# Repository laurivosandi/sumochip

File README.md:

# SumoCHIP

SumoCHIP is an extremely low-budget robotics platform based on CHIP single-board
computer. SumoCHIP is designed for teaching soldering, electronics, programming
and networking.

## Documentation

Bill of materials, instructions for building the robot and setting up the software are available [here](doc/index.md).
Translations are very much welcome.
See below how you can contribute!

## Demo

This is how the robot looks like once assembled:

Here's a video of two sumorobots battling in the sumo ring:

## Kits

Being completely open hardware you can order the components and assemble the
robot yourself with the prices stated in the [bill of materials](doc/bom.md) page,
expect to spend around 30 USD per robot.
Robotics Club of Estonian IT College provides kits within EU which saves
you the hassle of purchasing invidual components online.

| Description                                                    | Price                         |
|----------------------------------------------------------------|-------------------------------|
| SumoCHIP PCB and solderable components only                    | 20 EUR + recommended donation |
| Everything except [C.H.I.P.](http://getchip.com/products/chip) | 40 EUR + recommended donation |
| All in one batteries included kit                              | 50 EUR + recommended donation |

When ordering please specify whether you want PCB to be soldered or not,
soldered board adds extra 10 EUR to the price. We can also ship custom
configurations of components.
Donations are used to renew the equipment of robotics club so we could continue doing cool stuff!

To order send us e-mail and we'll reply with an invoice PDF.
Within EU standard [SEPA](https://en.wikipedia.org/wiki/Single_Euro_Payments_Area)
payments are expected. Once payment is received the kits will be shipped with
standard mail services once a week.

## Software

The current implementation is based on Python and Flask.
In future we might add
[kernel module for generating fine grained PWM signals](https://github.com/tanzilli/soft_pwm)
to achieve better timing granularity for servo motors.

## Contributing

Improvements and translations are very much welcome.
The contents of this Git repository are published under very liberal [MIT license](LICENSE).
Just register an account here at GitHub and hit the Fork button in the top right corner,
this shall make a copy of the source code repository under your GitHub account.
Make the necessary modifications in your repository and once ready
make a [pull request](https://help.github.com/articles/about-pull-requests/)
to get your changes merged. All contributors shall be mentioned in [the contributors list](CONTRIBUTORS.md).
We don't expect you to sign a contributor license agreement,
but you should not forget that as this project is distributed under MIT license,
third parties or even us are free to make commercial use of any of the repository's contents.

## Known issues

We are aware of following issues:

* Do not attempt to power servo motors without having battery connected. The servos simply drain too many amps which causes CHIP to power off if the power is supplied only over USB cable. This will not damage CHIP or your computer's USB ports, this is simply USB ports safety mechanism to prevent overcurrent.
* Certain USB 3.0 enabled motherboards have trouble connecting to CHIP over USB cable or the connection is occasionally lost under Ubuntu. Try to disable USB 3.0 in BIOS.
* Enemy detection sensors in their current form are very sensitive. Ambient light, especially direct sunlight triggers the phototransistors making it nearly impossible to use the robots outdoors. Proper shielding of phototransistors with black shrinktubes is crucial, use blinds to cover direct sunlight if necessary. Alternative sensors would increase the price of the robot significantly, that's the main reason why we sticked to primitive infrared LED and phototransistor pair method.
* Under Ubuntu add your user account to `dialout` group, log out from your desktop session and log in again. Otherwise your user account is unable to make use of the serial connection to CHIP, resulting in error `cannot open /dev/ttyACM0`.
* Running `sumochip-test` while the web interface is running in the background causes jerky behaviour, stop web interface first `systemctl stop sumochip`.
* Cheap servo motors tend to have jerky behaviour due to soft PWM jitter
* Touchscreen ADC-s will likely not be available for regular userspace apps, so no chance to connect analog sensors
* When NextThingCo enabled MLC for the storage CHIP-s storage has become extremely unstable, UBIFS is just not mature enough yet

Powering the robot:

* Powering CHIP up while power supply pins 3.3V or 5V are shorted to ground or to eachother will cause AXP209 power supply IC to die. Carefully examine with a multimeter that 3.3V, 5V and ground rails are not connected to eachother.
* Reversing the battery polarity irreversable damages AXP209 power supply IC on the CHIP. Be extra careful when connecting the battery.
* If the CHIP remains powered on only for few seconds or if AXP209 heats up too much then it's likely that AXP209 has been damaged by one of the ways mentioned above.

If you have fried your AXP209, you can try to replace it with a new one. Damaged AXP209 can lead to battery drainage which can lead to irreversible battery damage or in extreme cases make the battery explode.

## About

SumoCHIP is developed by [Robotics Club of Estonian IT College](http://robot.itcollege.ee)

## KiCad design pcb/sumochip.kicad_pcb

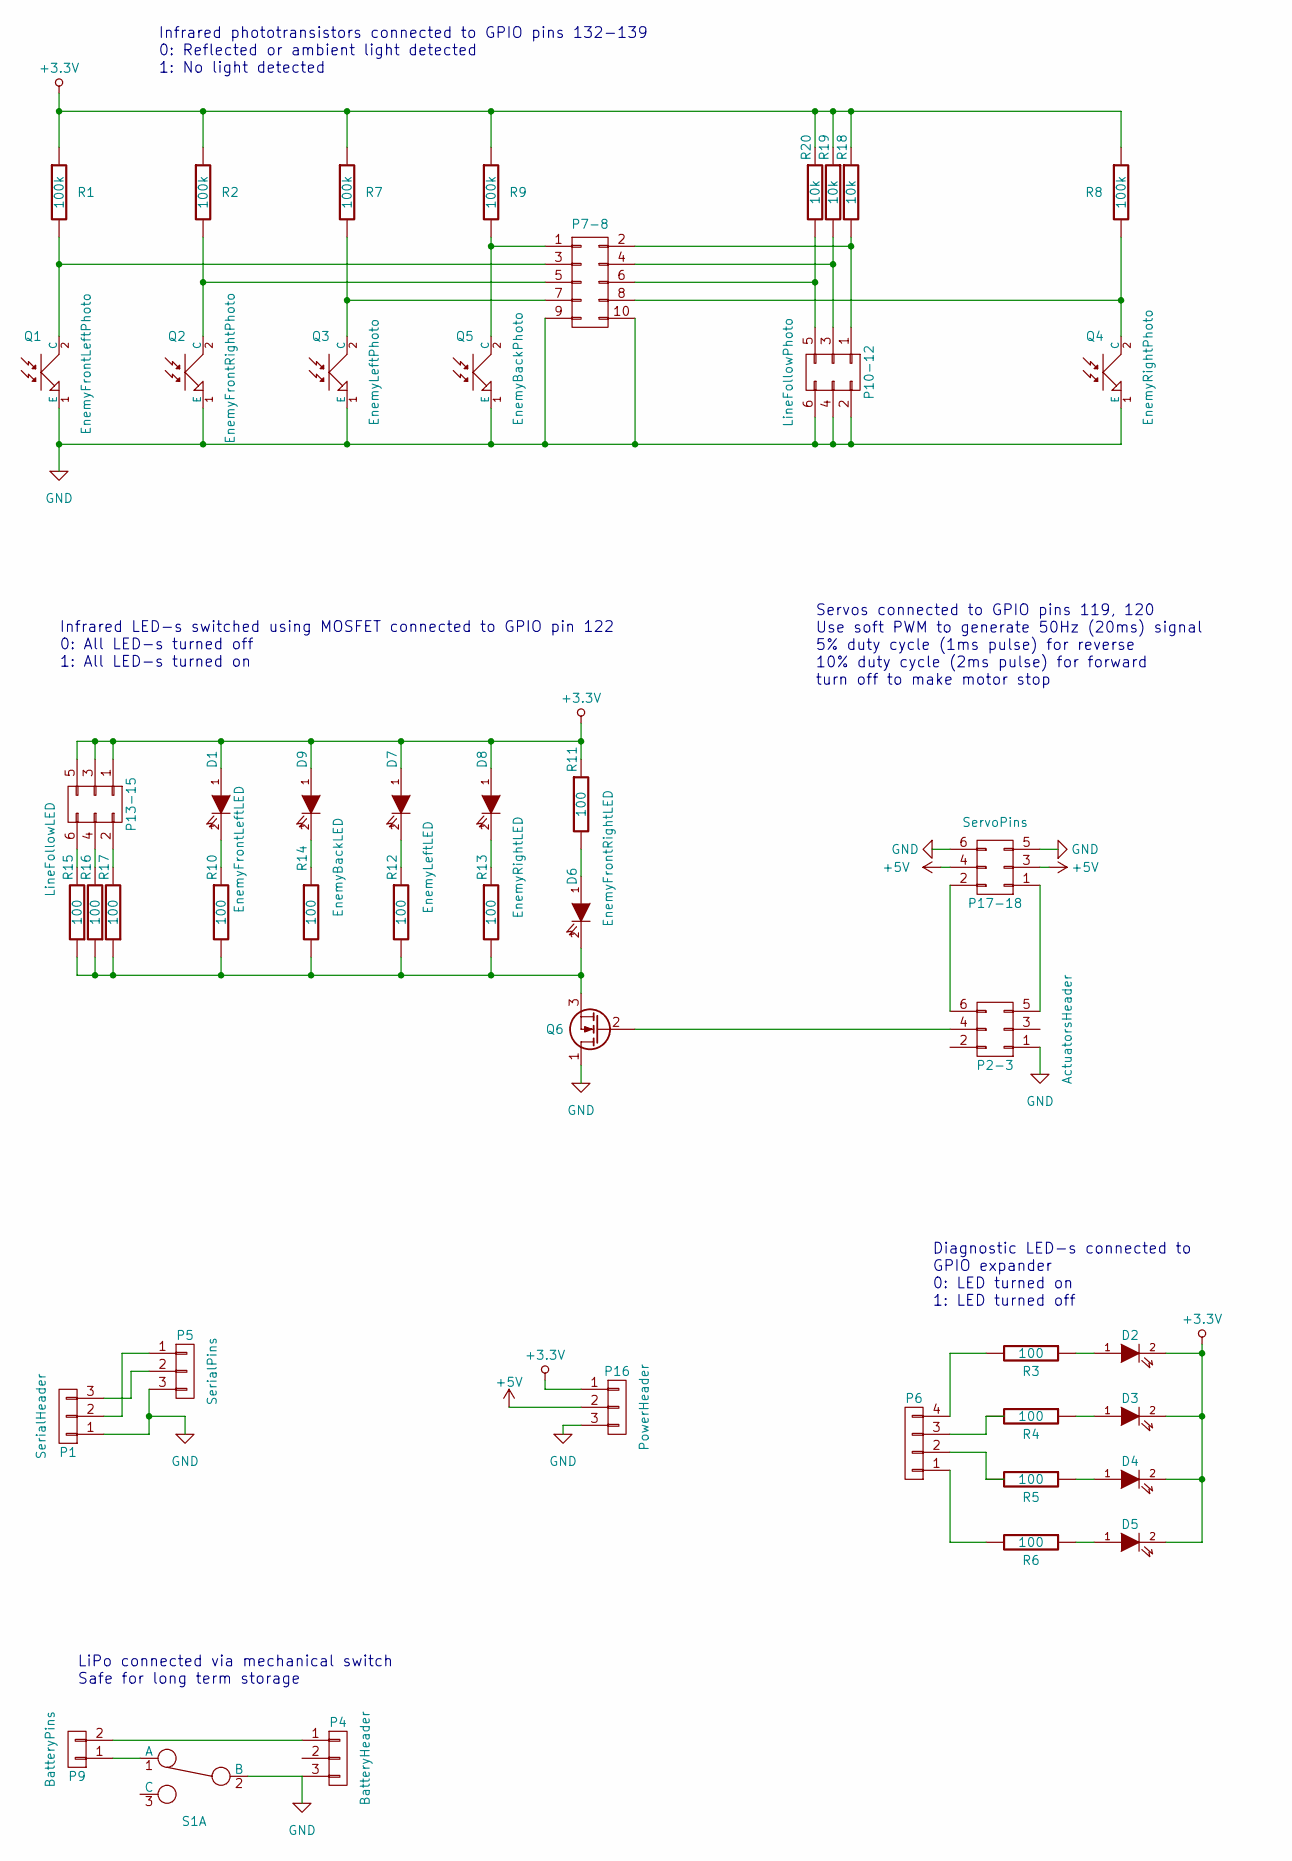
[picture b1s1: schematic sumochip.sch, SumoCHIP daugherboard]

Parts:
D1: EnemyFrontLeftLED; LED-3MM
D2, D3, D4, D5: LED; LED-3MM
D6: EnemyFrontRightLED; LED-3MM
D7: EnemyLeftLED; LED-3MM
D8: EnemyRightLED; LED-3MM
D9: EnemyBackLED; LED-3MM
P1: SerialHeader; Pin_Header_Straight_1x03
P2-3: ActuatorsHeader; Pin_Header_Straight_2x03
P4: BatteryHeader; Pin_Header_Straight_1x03
P5: SerialPins; Pin_Header_Angled_1x03
P6: DiagnosticHeader; Pin_Header_Straight_1x04
P7-8: SensorsHeader; Pin_Header_Straight_2x05
P9: BatteryPins; Pin_Header_Angled_1x02
P10-12: LineFollowPhoto; Pin_Header_Straight_2x03
P13-15: LineFollowLED; Pin_Header_Straight_2x03
P16: PowerHeader; Pin_Header_Straight_1x03
P17-18: ServoPins; Pin_Header_Straight_2x03
Q1: EnemyFrontLeftPhoto; LED-3MM
Q2: EnemyFrontRightPhoto; LED-3MM
Q3: EnemyLeftPhoto; LED-3MM
Q4: EnemyRightPhoto; LED-3MM
Q5: EnemyBackPhoto; LED-3MM
Q6: 2N7000; TO-92_Inline_Wide
R1, R2, R7, R8, R9: 100k; Resistor_Horizontal_RM10mm
R3, R4, R5, R6, R10, R11, R12, R13, R14, R15, R16, R17: 100; Resistor_Horizontal_RM10mm
R18, R19, R20: 10k; Resistor_Horizontal_RM10mm
S1: Switch_SPDT_x2; PINHEAD1-3

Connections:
+3.3V: D1.1 (A), D2.2 (K), D3.2 (K), D4.2 (K), D5.2 (K), D7.1 (A), D8.1 (A), D9.1 (A), P13-15.1, P13-15.3, P13-15.5, P16.1, R1.1, R2.1, R7.1, R8.1, R9.1, R11.1, R18.1, R19.1, R20.1
+5V: P16.2, P17-18.3, P17-18.4
GND: P1.1, P2-3.1, P4.3, P5.3, P7-8.9, P7-8.10, P10-12.2, P10-12.4, P10-12.6, P16.3, P17-18.5, P17-18.6, Q1.1 (E), Q2.1 (E), Q3.1 (E), Q4.1 (E), Q5.1 (E), Q6.1 (D), S1.2 (B); also elsewhere on the board
unnamed: D1.2 (K), R10.1
unnamed: D2.1 (A), R3.1
unnamed: D3.1 (A), R4.1
unnamed: D4.1 (A), R5.1
unnamed: D5.1 (A), R6.1
unnamed: D6.1 (A), R11.2
unnamed: D6.2 (K), Q6.3 (S), R10.2, R12.2, R13.2, R14.2, R15.1, R16.1, R17.1
unnamed: D7.2 (K), R12.1
unnamed: D8.2 (K), R13.1
unnamed: D9.2 (K), R14.1
unnamed: P1.2, P5.1
unnamed: P1.3, P5.2
unnamed: P2-3.4, Q6.2 (G)
unnamed: P4.1, P9.2
unnamed: P6.1, R6.2
unnamed: P6.2, R5.2
unnamed: P6.3, R4.2
unnamed: P6.4, R3.2
unnamed: P7-8.1, Q5.2 (C), R9.2
unnamed: P7-8.3, Q1.2 (C), R1.2
unnamed: P7-8.5, Q2.2 (C), R2.2
unnamed: P7-8.7, Q3.2 (C), R7.2
unnamed: P7-8.8, Q4.2 (C), R8.2
unnamed 26: P9.1, S1.1 (A); also elsewhere on the board
unnamed: P7-8.2, P10-12.1, R18.2
unnamed: P7-8.4, P10-12.3, R19.2
unnamed: P7-8.6, P10-12.5, R20.2
unnamed: P13-15.2, R17.2
unnamed: P13-15.4, R16.2
unnamed: P13-15.6, R15.2
unnamed: P2-3.5, P17-18.1
unnamed: P2-3.6, P17-18.2

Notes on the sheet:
Infrared LED-s switched using MOSFET connected to GPIO pin 122 0: All LED-s turned off 1: All LED-s turned on
Infrared phototransistors connected to GPIO pins 132-139 0: Reflected or ambient light detected 1: No light detected
Servos connected to GPIO pins 119, 120 Use soft PWM to generate 50Hz (20ms) signal 5% duty cycle (1ms pulse) for reverse 10% duty cycle (2ms pulse) for forward turn off to make motor stop
Diagnostic LED-s connected to GPIO expander 0: LED turned on 1: LED turned off
LiPo connected via mechanical switch Safe for long term storage

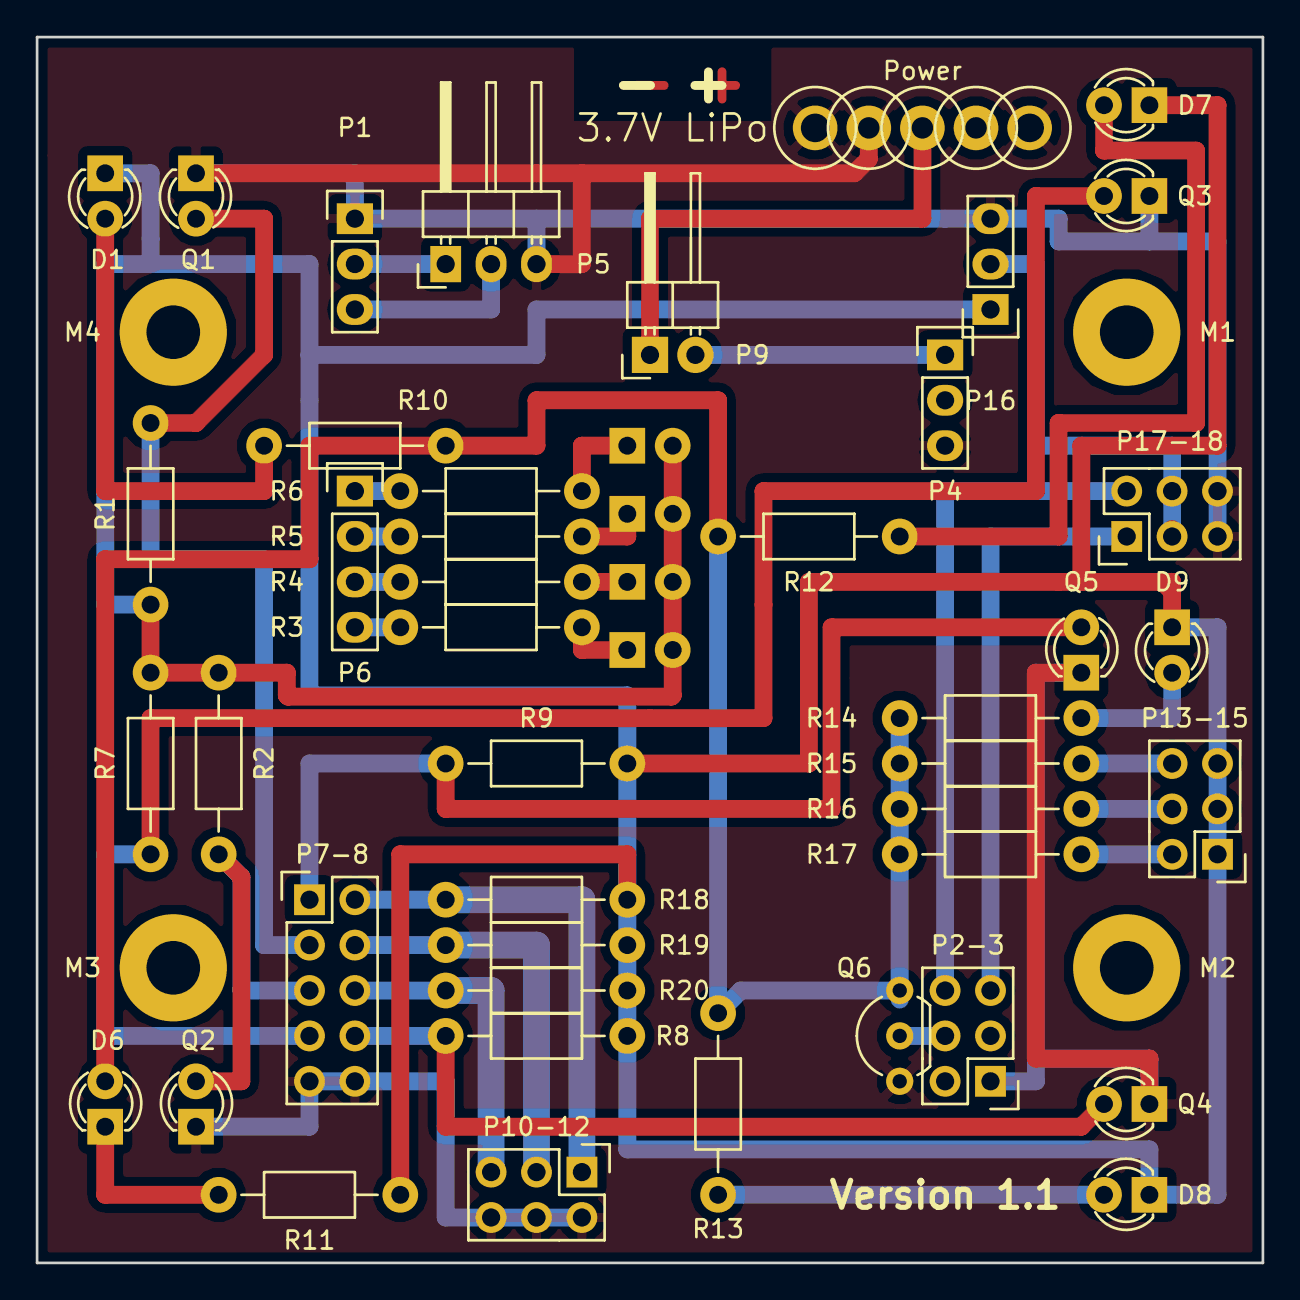
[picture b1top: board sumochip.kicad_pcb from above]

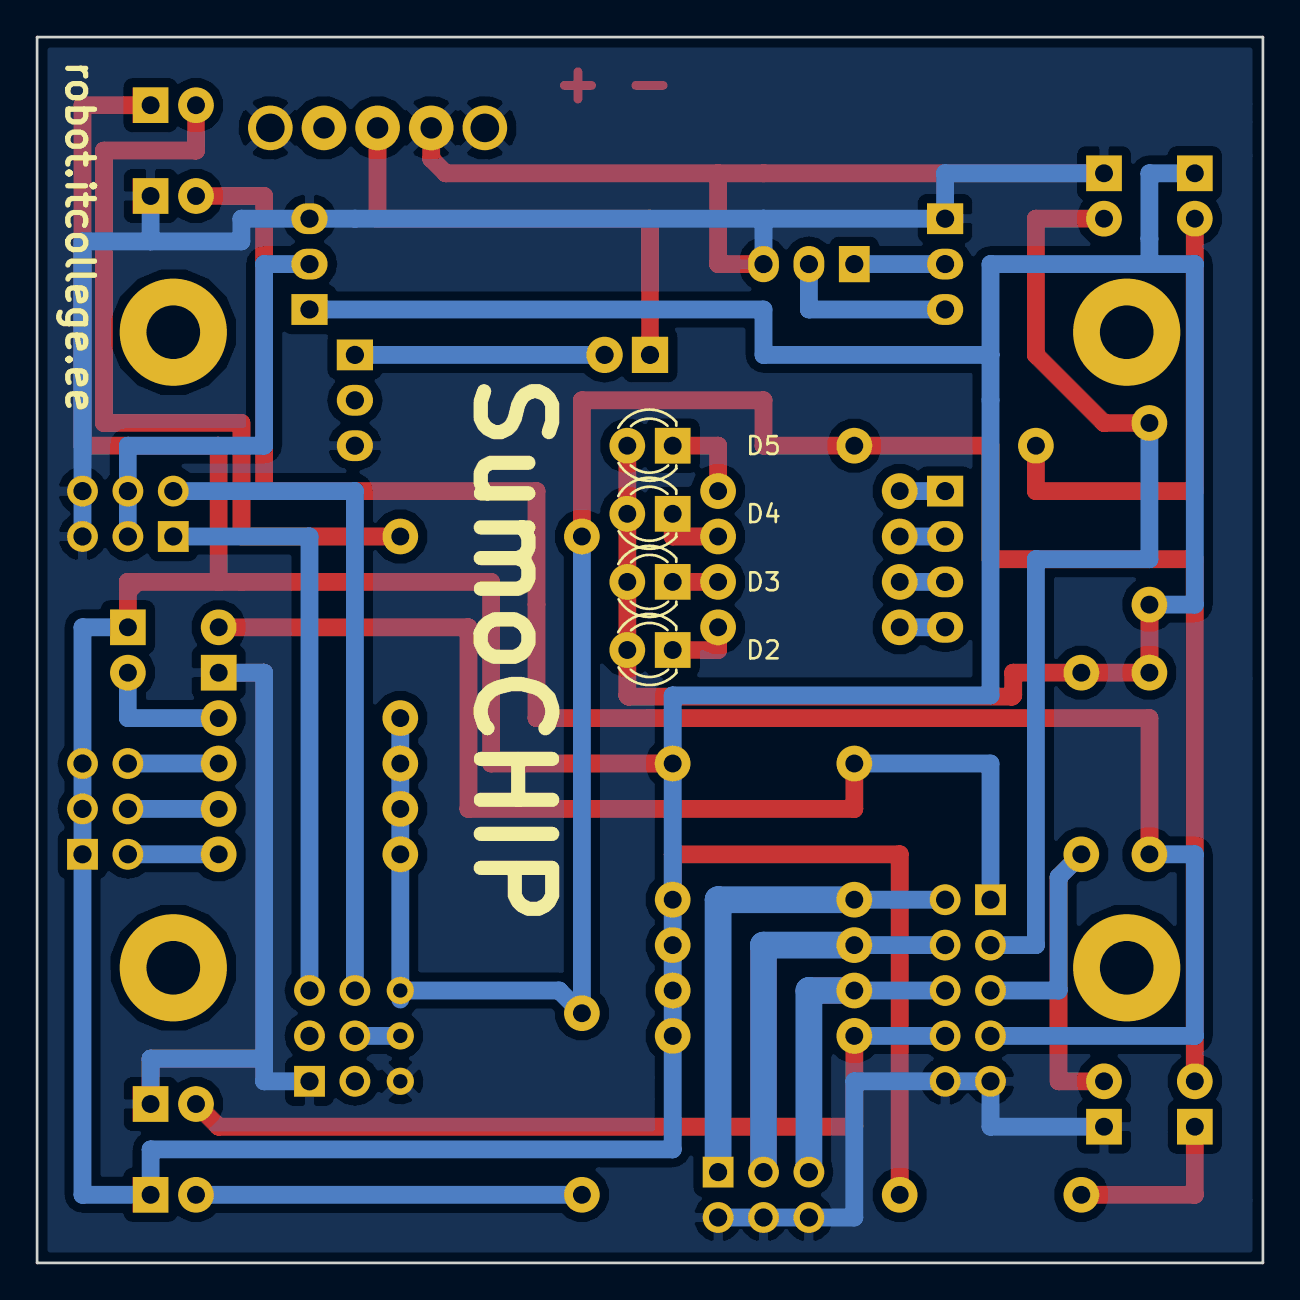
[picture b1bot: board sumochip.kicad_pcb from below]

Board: 2 copper layers, 68.6 x 68.6 mm, 55 parts (4 on the bottom side), 35 nets.

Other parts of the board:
M1, M2, M3, M4: SolderWirePad_single_2-5mmDrill
Power: 1pin
sw1, sw2, sw4, sw5: 1pin

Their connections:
GND: sw1.1, sw4.1, sw5.1; also elsewhere on the board
unnamed 26: Power.1; also elsewhere on the board

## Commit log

2016-05-07 Add software PWM snippet for driving servos
2016-05-19 Roboweb
2016-05-19 Remove ~ files
2016-06-11 Add bill of materials and update README
2016-06-11 Attempt to fix tables
2016-06-11 Another attempt to fix BOM table
2016-06-11 Add reference to homepage
2016-07-04 Add 3D model rendering
2016-07-09 Update BOM
2016-07-09 Add CONTRIBUTORS
2016-07-09 Fix typo
2016-07-18 Add preliminary Estonian documentation for robot assembly
2016-08-05 Add PCB design
2016-08-11 Working spaghetti
2016-08-11 Typo fix
2016-08-16 more code and configs
2016-08-17 Change config handling and no real HW mode
    * Sumorobot library can now read the config file from
    /etc/sumorobot/sumorobot.ini or
    ./sumorobot.ini
    * that .ini file can be a symlink to a real config
    * SumoChip HW v1.0 and v1.1 have now seperate config files.
    * Sumorobot code can now run without any real hardware.
2016-08-17 Config parser bug fix and change sensor_power pin on sumochip v1.1
2016-08-19 Config file updates, web interface doesn't chrash anymore
2016-08-19 Enabled line sensors
2016-08-19 Half finished user code execution implementation
2016-08-20 Add readme
2016-08-20 Working webinterface with battery gauge
    pointer cursor for buttons on the web
2016-08-20 Remove default sumorobot.ini symlink form repo
2016-08-20 Invert enemy sensors
2016-08-20 fix sensors
2016-08-20 Fix sensor reading
2016-08-20 Sometimes sensor read returns empty string
2016-08-21 Read all IO values through the IOProxy and IOPollThread
2016-08-21 Read axp209 i2c bus as int from config file
2016-08-21 Fix axp209 bus number in config files
2016-08-21 Print out config file that is used
2016-08-21 make sensors also use the ChipIO library
2016-08-21 Fix the damn sensors
2016-08-21 ChipIO was a bad idea
2016-08-21 Fix the sensors
2016-08-21 Fix the sensor fix
2016-08-21 Fix charge indicator
2016-08-21 Sample code
2016-08-22 Disable the text selection
2016-08-25 Add SumoCHIP PCB v1.1 schematic and layout
2016-08-26 Add setup.py
2016-08-26 configs
2016-08-27 Add systemd service
2016-08-27 Update sumochip software readme
2016-08-28 Add circuit and PCB layout rendered in SVG
2016-08-28 Add documentation
2016-08-28 Add image of components
2016-08-28 Add photos
2016-08-28 Use board instead of full page for PCB layout SVG rendering
2016-08-28 Fix typos and PCB layout image URL
2016-08-30 Add links
2016-08-30 Revert rename
2016-08-30 Fix URL
2016-08-31 Add USB serial driver installation instructions for Windows 10
2016-08-31 Add Windows driver installation instructions
2016-09-06 Add logos
2016-09-06 Insert logos to README
2016-09-07 Added english version.
2016-09-07 Added english version. Actually included the files this time.
2016-09-07 Typo fix..
2016-09-09 Improved installation notes about serial connection.
2016-09-09 Add Matteo as contributor
2016-09-09 Add logos to Estonian docs
2016-09-11 Add Karell as contributor
2016-09-11 Restore logos in README
2016-09-11 Add notice about contributing
2016-09-11 Clarify contributing conditions
2016-09-11 Add mcedit screenshot
2016-09-11 Clarify LICENSE
2016-09-12 Add link to soft PWM kernel
2016-09-12 Fix links
2016-09-12 Another attempt to fix the links
2016-09-12 Yet another attempt to fix the darn links
2016-09-12 Relative links are broken, attempt to restructure pages
2016-09-12 Improve English docs
2016-09-14 Add link to Youtube video
2016-09-14 Add photo of the robot
2016-09-14 We failed to keep PCB design single-sided
    The circuit is just too complex to implement on single side without significantly increasing the size of the PCB
2016-09-15 Disable the zooming from mobile web interface
2016-09-16 Add plow template
2016-09-23 Add missing image of OPB745
2016-10-11 Add known issues: dialout group, jerky servo behaviour
2016-10-11 Create a lockfile that allows only one instance of sumochip to run.
2016-10-11 Add animated image of assembly
2016-12-12 Refactor and add missing files
    * Remove sumochip.service
    * Add sumochip-setup script
    * Corrected XIO pin numbers and adjusted servo timings
    * Fix bugs in sumorobot.py
    * Add missing documentation images
2016-12-13 Revert priority settings
2016-12-13 Create /etc/sumorobot and fix typo
2017-05-12 Fix README headings
2017-05-12 List more known issues
